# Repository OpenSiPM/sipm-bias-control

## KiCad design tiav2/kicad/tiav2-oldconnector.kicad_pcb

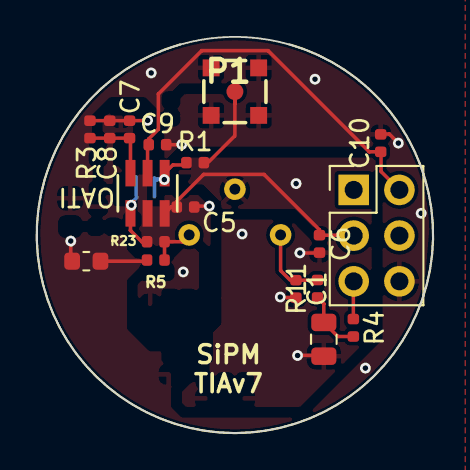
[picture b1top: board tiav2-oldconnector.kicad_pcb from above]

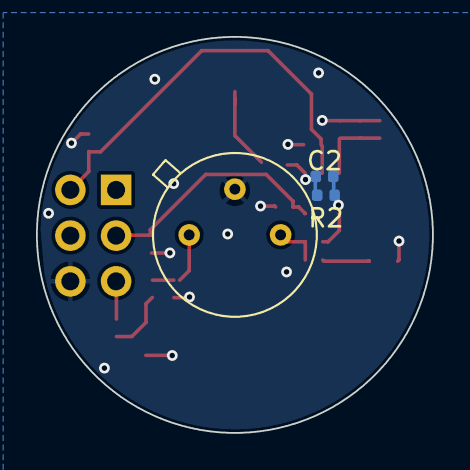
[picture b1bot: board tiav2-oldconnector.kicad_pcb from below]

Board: 2 copper layers, 22.0 x 22.0 mm, 21 parts (3 on the bottom side), 12 nets.

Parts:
C1, C5, C7, C9: 0.1u; C_0402_1005Metric
C2: 1.8p; C_0402_1005Metric
C3: 1u; C_0805_2012Metric
C6, C10: 4.7u; C_0402_1005Metric
C8: 100p; C_0402_1005Metric
D1: SIPM; S14420
J1: SSQ-103-01-G-D; PinHeader_2x03_P2.54mm_Vertical
L1: 0.4uH; L_0603_1608Metric
P1: 73415-2061; 73415-2063
R1: 50; R_0402_1005Metric
R2, R3: 1.5k; R_0402_1005Metric
R4, R11: 36; R_0402_1005Metric
R5: 10; R_0402_1005Metric
R23: 100; R_0402_1005Metric
U1: OPA847IDBVT

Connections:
+VDC: J1.5, R4.1
/OUT: P1.1, R1.2
/VBiasFilt: C1.1, D1.1, R11.2
GND: C1.2, C3.2, C5.2, C6.2, C7.2, C8.2, C9.2, C10.2, D1.3, J1.6, L1.2, P1.2, P1.3, P1.4, P1.5, R3.1
unnamed: C2.1, R2.1, R23.2, U1.4
unnamed: C2.2, R1.1, R2.2, U1.1
unnamed: C3.1, R4.2, R11.1
unnamed: C7.1, C8.1, R3.2, U1.3
unnamed: D1.2, R5.2, R23.1
unnamed: L1.1, R5.1
VDDA: C5.1, C6.1, J1.3, U1.6
VSSA: C9.1, C10.1, J1.2, U1.2

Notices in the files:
parts and their libraries:
Copyright 2016 Accelerated Designs. All rights reserved.
